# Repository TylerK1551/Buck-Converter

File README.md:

# 12V to 5V Synchronous Buck Converter

A 5V, 3A synchronous buck converter built around the Renesas ISL6545A voltage-mode PWM controller with external MOSFETs, designed end to end in KiCad.

I took this board from schematic capture through a custom controller symbol, footprint and 3D model assignment, two-layer placement and routing, DRC, and fabrication outputs. Most of the design effort went into the layout decisions that make or break a switching converter: the hot loop, the switch node, the ground plane, and the feedback path.

**Status:** Designed and DRC-clean. Not yet fabricated or tested. The plan for bring-up is at the end of this page.

## Specs

| Parameter | Value |
|---|---|
| Input | 12V (controller VCC and power stage VIN share the rail) |
| Output | 5.0V |
| Output current | 3A |
| Controller | Renesas ISL6545A, voltage mode, 600kHz fixed |
| Switches | 2x AOS AOD4184A, 40V N-channel, DPAK |
| Inductor | 4.7µH, Bourns SRP7028A-4R7M (10A sat) |
| Output capacitor | 330µF 10V polymer, Panasonic 10SVP330MX |
| Board | 55 x 58 mm, 2 layers |
| Tools | KiCad 10 |

## Design notes

### Hot loop
The loop from the input ceramic (C8) through the high-side FET, the switch node, the low-side FET and back to C8 carries the fast current edges, so I placed it first and kept it as tight as I could. It took a few iterations: rotating Q2 shortened the switch node connection but made the ground return long, so I moved C8 to the other side of the FETs where it bridges Q1's drain tab and Q2's source directly.

The +12V leg of the loop is a filled zone, and both the +12V zone and the power pads use solid connections instead of thermal reliefs so the pulsed current isn't forced through thin spokes.

### Switch node
The switch node copper is only wide where load current actually flows (Q1 source to Q2 tab to L1). The branch to PHASE and the bootstrap cap carries only gate drive current, so it's a thin trace that leaves from right next to Q1's source instead of from the inductor end.

### Input path
J1 feeds the bulk cap (C7) first and then the FETs, so the bulk capacitor sits in the current path rather than on a side branch.

### Compensation
The datasheet's typical application shows Type II compensation, but with a low-ESR polymer output cap the ESR zero sits too high for Type II to give comfortable phase margin across part tolerances. I added R3 and C5 across the upper feedback resistor to make it Type III, which is what the datasheet recommends for general use. Values follow the datasheet's design procedure. Stability still needs to be confirmed with a load step once the board is built.

### Output voltage and remote sensing
Vout = 0.6V x (1 + 2.2k / 300) = 5.0V. The top of the feedback divider connects to J2's +5V pad with its own trace (a Kelvin connection), so the converter regulates the voltage at the output terminal and no load current flows through the sense path.

### Overcurrent
The ISL6545A senses current across the low-side FET's Rds(on). ROCSET (R5 = 1.5k) puts the worst-case trip (hot FET, minimum OCSET current) around 5A, above the roughly 3.5A peak inductor current at full load, and the typical trip stays under the inductor's 10A saturation rating.

### Ground plane and layer use
The bottom layer is a solid GND plane. Top-side ground pads drop to it through vias, with the most vias at C8 and Q2's source where the pulsed return current is. Only two signals use the bottom layer: LGATE (boxed in by the switch node and PHASE on top) and VCC. Both are thin and kept away from the area under the hot loop to limit slots in the plane.

### Tradeoffs
- PHASE runs under U1 between the pad rows. It was the only single-layer path that didn't cross UGATE or the FB/COMP traces, and I chose it over another via to keep the ground plane intact. The downside is that it passes near the FB pin. In a revision I'd look at re-orienting U1 so PHASE doesn't need to go there.
- UGATE and PHASE can't run side by side the whole way because of where the pins sit, so I prioritized keeping UGATE short and direct.

## Bill of materials

| Ref | Value | Part / spec | Function |
|---|---|---|---|
| U1 | ISL6545A | ISL6545AIBZ, SOIC-8 | Controller |
| Q1 | 40V N-FET | AOS AOD4184A, DPAK | High-side switch |
| Q2 | 40V N-FET | AOS AOD4184A, DPAK | Low-side switch |
| L1 | 4.7µH | Bourns SRP7028A-4R7M | Output inductor |
| C6 | 330µF 10V | Panasonic 10SVP330MX | Output capacitor |
| C7 | 100µF 25V | Low-ESR aluminum electrolytic | Input bulk |
| C8 | 10µF 25V | X7R, 1206 | Input HF decoupling (hot loop) |
| C4 | 0.1µF 25V | X7R, 0603 | Bootstrap |
| C3 | 1µF 25V | X7R, 0805 | VCC decoupling |
| R4 | 2.2k 1% | 0603 | Feedback divider, top |
| R2 | 300 1% | 0603 | Feedback divider, bottom |
| R1 | 3.3k 1% | 0603 | Compensation |
| C2 | 22nF | 0603 | Compensation |
| C1 | 1.5nF | C0G, 0603 | Compensation |
| R3 | 22 1% | 0603 | Compensation (Type III) |
| C5 | 15nF | 0603 | Compensation (Type III) |
| R5 | 1.5k 1% | 0603 | Overcurrent set (ROCSET) |
| J1 | 2-pin | MaiXu MX126-5.0-02P, 5mm screw terminal | 12V input |
| J2 | 2-pin | MaiXu MX126-5.0-02P, 5mm screw terminal | 5V output |

## Repository layout

- `Buck Converter.kicad_pro`, `.kicad_sch`, `.kicad_pcb`: KiCad project, schematic and PCB
- `controller_symbol.kicad_sym`: custom ISL6545A symbol
- `gerbers/`: Gerber and drill files for fabrication
- `3D Files/`: STEP models that aren't in the default KiCad library

## Next steps

- Fabricate and verify: switch node ringing, load-step response, efficiency and FET temperatures at 3A
- Re-orient U1 to get PHASE away from FB
- Add mounting holes

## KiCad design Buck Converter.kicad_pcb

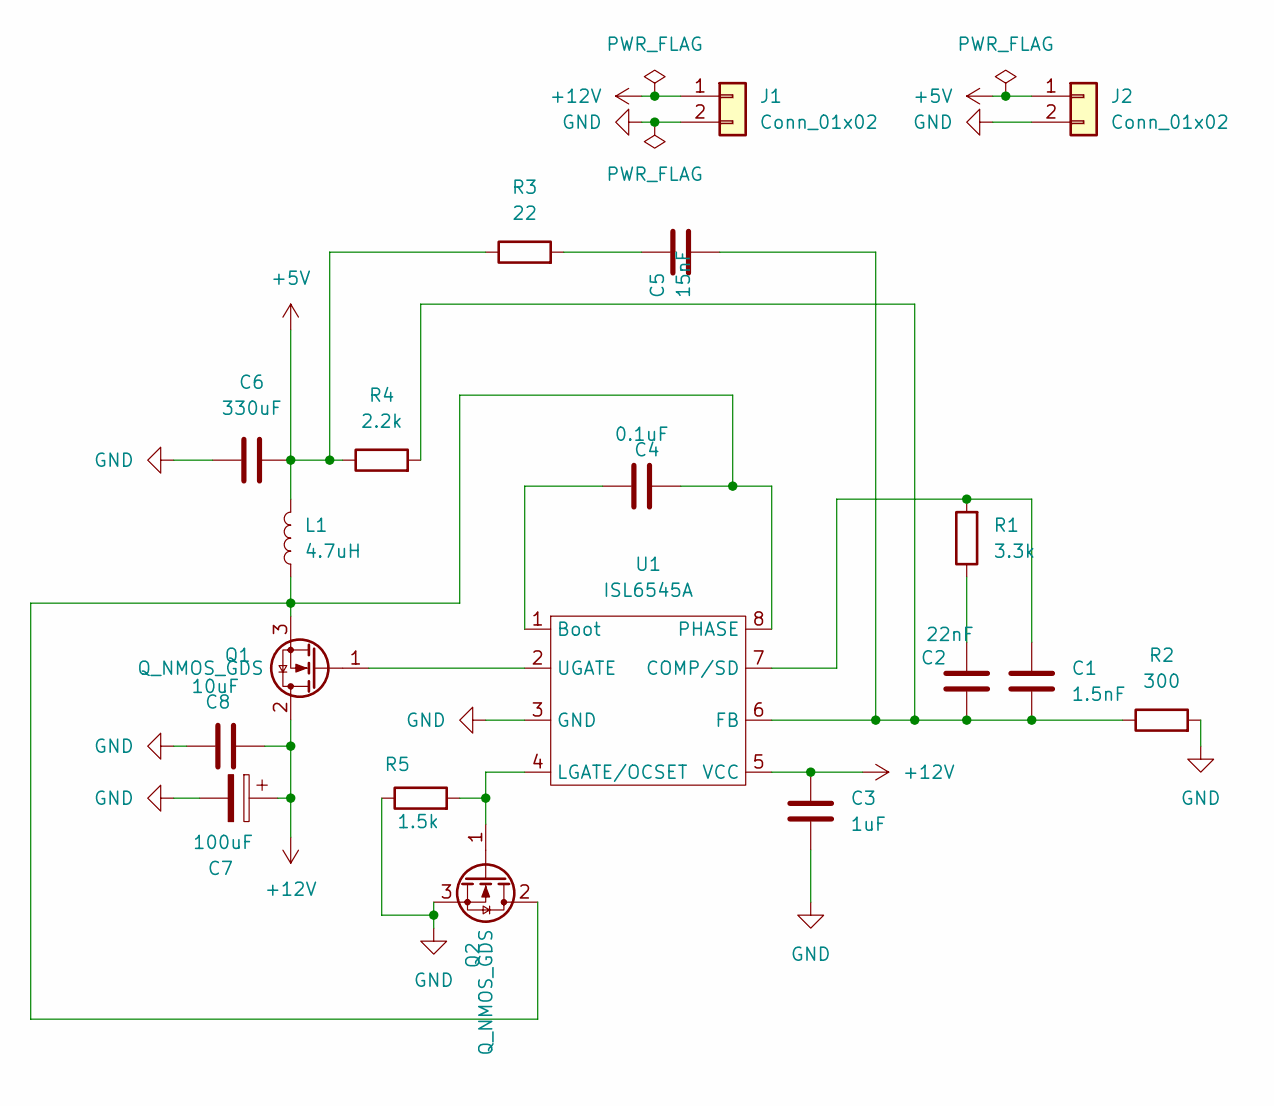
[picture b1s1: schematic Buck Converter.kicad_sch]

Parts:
C1: 1.5nF; C_0603_1608Metric
C2: 22nF; C_0603_1608Metric
C3: 1uF; C_0805_2012Metric
C4: 0.1uF; C_0603_1608Metric
C5: 15nF; C_0603_1608Metric
C6: 330uF; CP_Elec_10x7.9
C7: 100uF; CP_Elec_8x10
C8: 10uF; C_1206_3216Metric
J1, J2: Conn_01x02; TerminalBlock_MaiXu_MX126-5.0-02P_1x02_P5.00mm
L1: 4.7uH; L_Bourns_SRP7028A_7.3x6.6mm
Q1, Q2: Q_NMOS_GDS; TO-252-2
R1: 3.3k; R_0603_1608Metric
R2: 300; R_0603_1608Metric
R3: 22; R_0603_1608Metric
R4: 2.2k; R_0603_1608Metric
R5: 1.5k; R_0603_1608Metric
U1: ISL6545A; SOIC-8_3.9x4.9mm_P1.27mm

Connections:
+5V: C6.2, J2.1, L1.2, R3.1, R4.1
+12V: C3.1, C7.1, C8.2, J1.1, Q1.2 (D), U1.5 (VCC)
GND: C3.2, C6.1, C7.2, C8.1, J1.2, J2.2, Q2.3 (S), R2.2, R5.1, U1.3 (GND)
unnamed: C2.2, R1.1
unnamed: C5.2, R3.2
unnamed: Q1.1 (G), U1.2 (UGATE)
unnamed: C4.2, L1.1, Q1.3 (S), Q2.2 (D), U1.8 (PHASE)
unnamed: Q2.1 (G), R5.2, U1.4 (LGATE/OCSET)
unnamed: C4.1, U1.1 (Boot)
unnamed: C1.2, R1.2, U1.7 (COMP/SD)
unnamed: C1.1, C2.1, C5.1, R2.1, R4.2, U1.6 (FB)

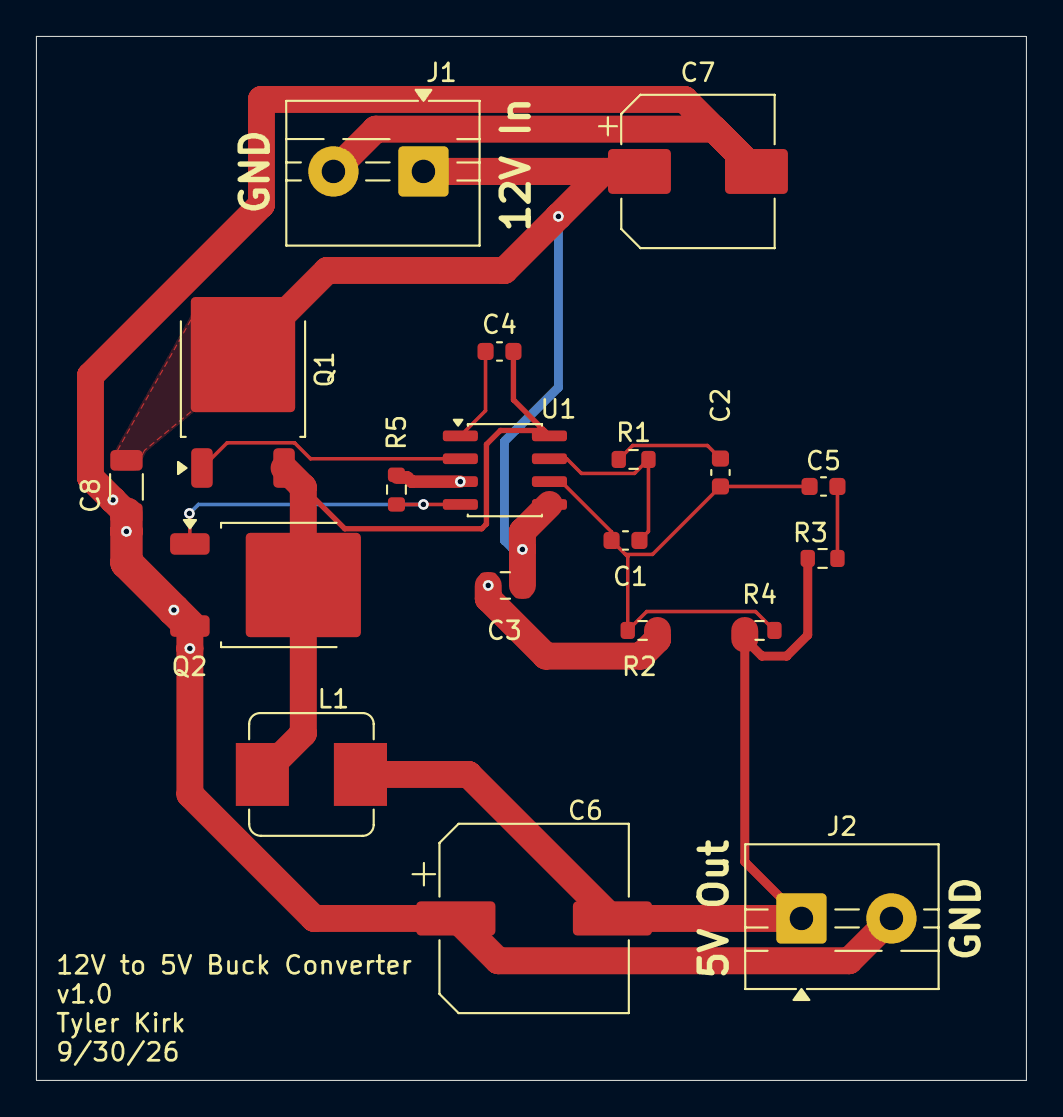
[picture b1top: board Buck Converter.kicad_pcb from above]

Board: 2 copper layers, 55.0 x 58.0 mm, 19 parts (0 on the bottom side), 11 nets.
